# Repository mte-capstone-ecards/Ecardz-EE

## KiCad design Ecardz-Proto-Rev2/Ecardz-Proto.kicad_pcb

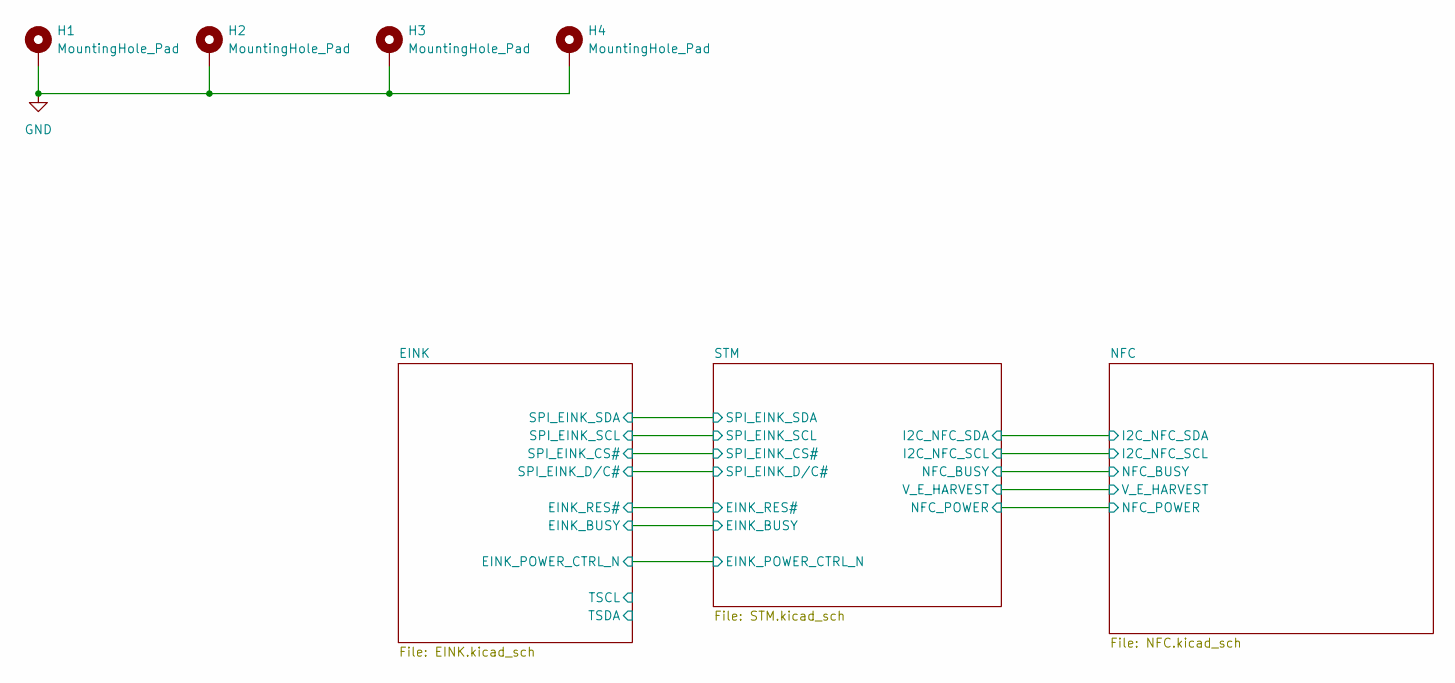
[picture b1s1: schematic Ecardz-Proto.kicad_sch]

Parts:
H1, H2, H3, H4: MountingHole_Pad; MountingHole_2.2mm_M2_DIN965

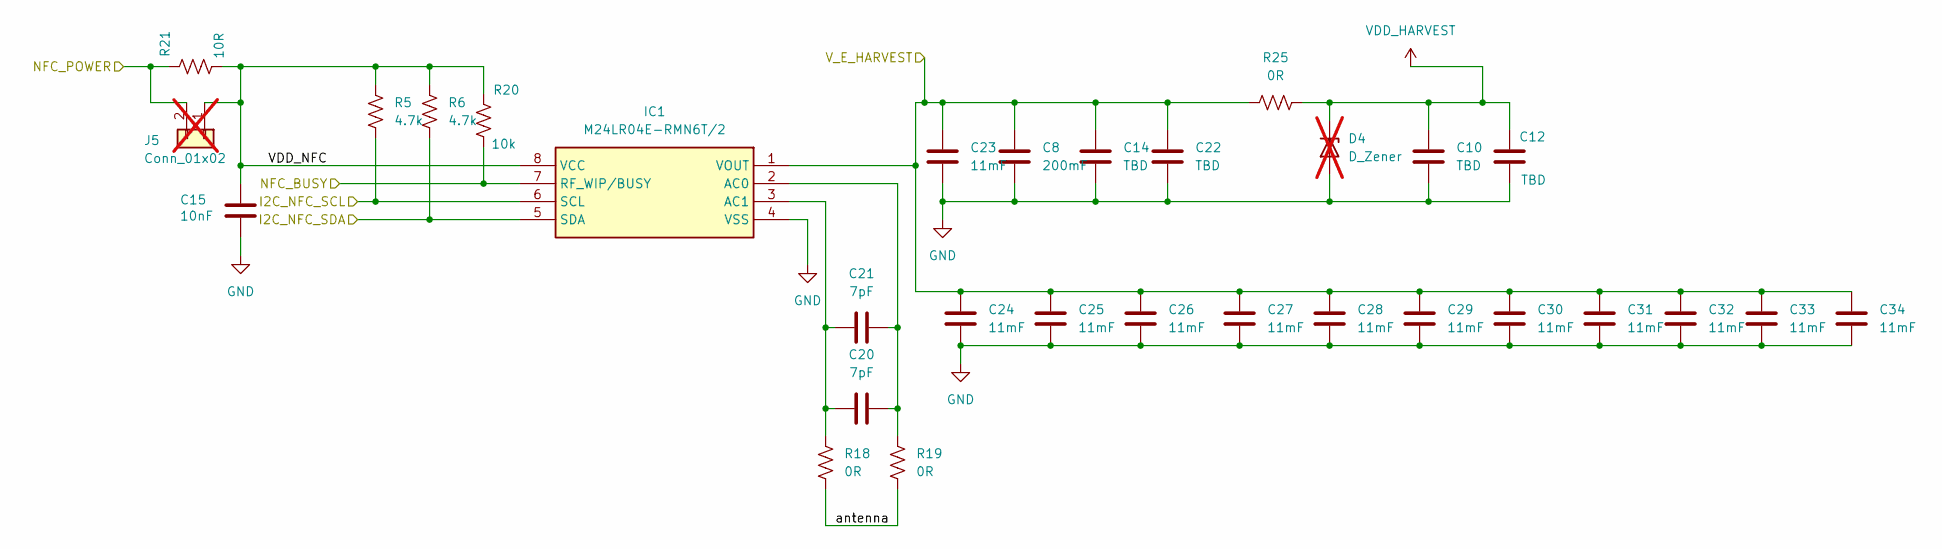
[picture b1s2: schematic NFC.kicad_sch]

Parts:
C8: 200mF; RSCSK2043R3D01004T; Digikey Part Number SCSK2043R3D01004T
C10, C12: TBD; C_0603_1608Metric_Pad1.08x0.95mm_HandSolder
C14, C22: TBD; C_2917
C15: 10nF; C_0603_1608Metric_Pad1.08x0.95mm_HandSolder; MANUFACTURER PART NUMBER C0603C102K5RACTU; Digikey Part Number 399-C0603C102K5RACTUTR-ND
C20, C21: 7pF; C_0603_1608Metric_Pad1.08x0.95mm_HandSolder; MANUFACTURER PART NUMBER GRM0335C1E7R0CA01D; Digikey Part Number 490-13324-2-ND
C23, C24, C25, C26, C27, C28, C29, C30, C31, C32, C33, C34: 11mF; CPH3225A; Digikey Part Number CPH3225A
D4: D_Zener; D_SOD-123; MANUFACTURER PART NUMBER MMSZ4684T1G; Digikey Part Number MMSZ4684T1GOSTR-ND; not fitted
IC1: M24LR04E-RMN6T/2; SO-8_3.9x4.9mm_P1.27mm; Mouser Part Number 511-M24LR04E-RDW6T/2
J5: Conn_01x02; PinHeader_1x02_P2.54mm_Vertical; not fitted
R5, R6: 4.7k; R_0603_1608Metric_Pad0.98x0.95mm_HandSolder; Part Number ERJ-3EKF4701V
R18, R19, R25: 0R; R_0603_1608Metric_Pad0.98x0.95mm_HandSolder; MANUFACTURER PART NUMBER CRCW0603590RFKEA; Digikey Part Number 541-590HTR-ND
R20: 10k; R_0603_1608Metric_Pad0.98x0.95mm_HandSolder; MANUFACTURER PART NUMBER RC0603FR-0710KL; Digikey Part Number 311-10.0KHRTR-ND
R21: 10R; R_0603_1608Metric_Pad0.98x0.95mm_HandSolder; MANUFACTURER PART NUMBER NRC06J100TRF

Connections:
/NFC/NFC_POWER: J5.2, R21.1; also elsewhere on the board
/NFC/VDD_NFC: C15.1, IC1.8 (VCC), J5.1, R5.1, R6.1, R20.1, R21.2
/NFC/V_E_HARVEST: C8.1, C14.1, C22.1, C23.1, C24.1, C25.1, C26.1, C27.1, C28.1, C29.1, C30.1, C31.1, C32.1, C33.1, C34.1, IC1.1 (VOUT), R25.1; also elsewhere on the board
/NFC/antenna: R18.1, R19.1
/STM/I2C_NFC_SCL: IC1.6 (SCL), R5.2; also elsewhere on the board
/STM/I2C_NFC_SDA: IC1.5 (SDA), R6.2; also elsewhere on the board
/STM/NFC_BUSY: IC1.7 (RF_WIP/BUSY), R20.2; also elsewhere on the board
GND: C8.2, C10.2, C12.2, C14.2, C15.2, C22.2, C23.2, C24.2, C25.2, C26.2, C27.2, C28.2, C29.2, C30.2, C31.2, C32.2, C33.2, C34.2, D4.2 (A), IC1.4 (VSS); also elsewhere on the board
unnamed: C20.2, C21.2, IC1.2 (AC0), R19.2
unnamed: C20.1, C21.1, IC1.3 (AC1), R18.2
VDD_HARVEST: C10.1, C12.1, D4.1 (K), R25.2; also elsewhere on the board

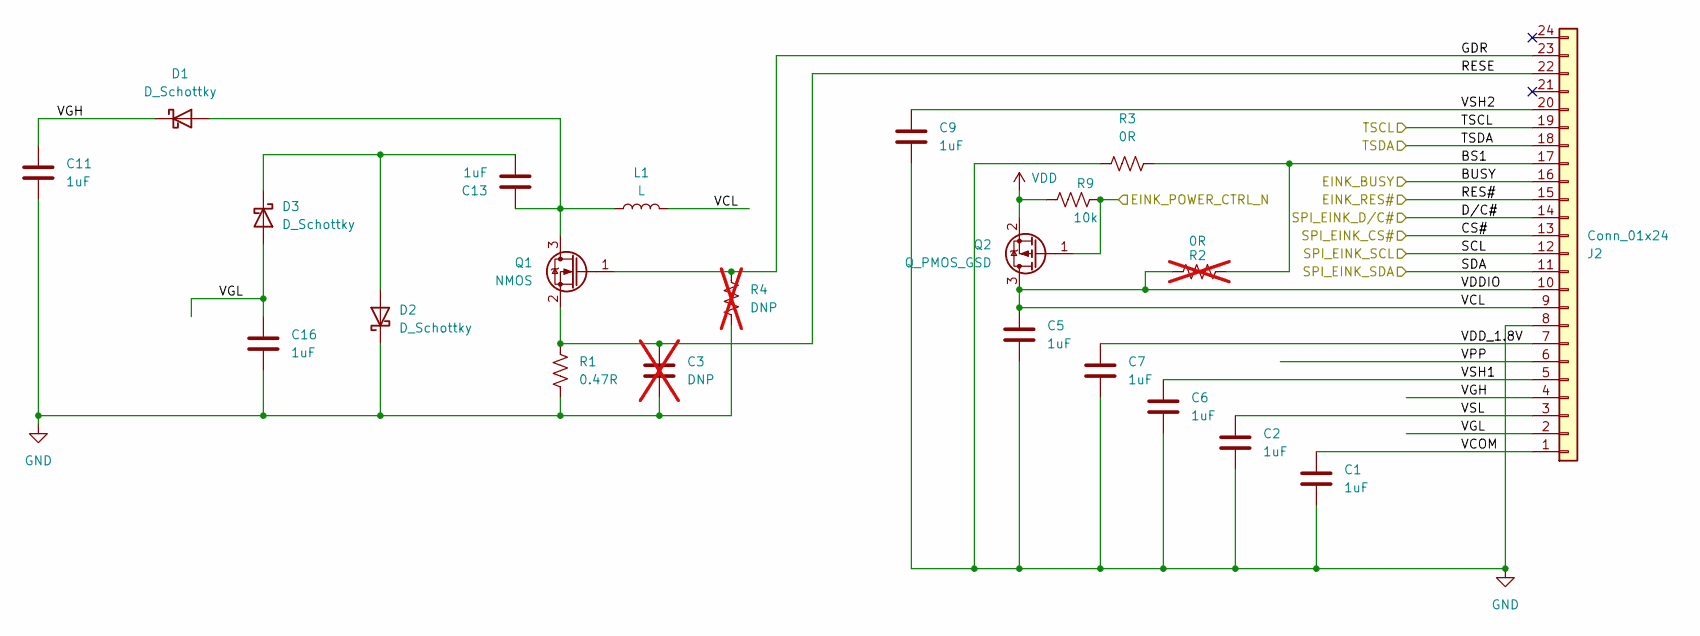
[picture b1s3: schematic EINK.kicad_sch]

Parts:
C1, C2, C5, C6, C7, C9, C11, C13, C16: 1uF; C_0603_1608Metric_Pad1.08x0.95mm_HandSolder; MANUFACTURER PART NUMBER CC0603KRX5R8BB105; Digikey Part Number 311-1445-2-ND
C3: DNP; C_0603_1608Metric_Pad1.08x0.95mm_HandSolder; MANUFACTURER PART NUMBER 100pF; not fitted
D1, D2, D3: D_Schottky; D_SOD-123; MANUFACTURER PART NUMBER MBR0530T1G; Digikey Part Number MBR0530T1GOSTR-ND
J2: Conn_01x24; TE_2-1734839-4_1x24-1MP_P0.5mm_Horizontal; MANUFACTURER PART NUMBER 4-1734839-5; Digikey Part Number A101358TR-ND
L1: L; CDRH5D18; MANUFACTURER PART NUMBER CDRH5D18NP-470NC; Digikey Part Number 308-2060-2-ND
Q1: NMOS; SOT-23; MANUFACTURER PART NUMBER IRLML2803TRPBF; Digikey Part Number IRLML2803PBFTR-ND
Q2: Q_PMOS_GSD; SOT-23; MANUFACTURER PART NUMBER BSS138NH6433XTMA1
R1: 0.47R; R_0603_1608Metric_Pad0.98x0.95mm_HandSolder; MANUFACTURER PART NUMBER ERJ-3RQJR47V; Digikey Part Number ERJ-3RQJR47V
R2: 0R; R_0603_1608Metric_Pad0.98x0.95mm_HandSolder; MANUFACTURER PART NUMBER RC0603JR-070RL; Digikey Part Number 311-0.0GRTR-ND; not fitted
R3: 0R; R_0603_1608Metric_Pad0.98x0.95mm_HandSolder; MANUFACTURER PART NUMBER RC0603JR-070RL; Digikey Part Number 311-0.0GRTR-ND
R4: DNP; R_0603_1608Metric_Pad0.98x0.95mm_HandSolder; MANUFACTURER PART NUMBER 100kR; not fitted
R9: 10k; R_0603_1608Metric_Pad0.98x0.95mm_HandSolder; MANUFACTURER PART NUMBER RC0603FR-0710KL; Digikey Part Number 311-10.0KHRTR-ND

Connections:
/EINK/BS1: J2.17, R2.2, R3.2
/EINK/BUSY: J2.16; also elsewhere on the board
/EINK/CS#: J2.13; also elsewhere on the board
/EINK/D/C#: J2.14; also elsewhere on the board
/EINK/EINK_POWER_CTRL_N: Q2.1 (G), R9.2; also elsewhere on the board
/EINK/GDR: J2.23, Q1.1 (G), R4.1
/EINK/RES#: J2.15; also elsewhere on the board
/EINK/RESE: C3.1, J2.22, Q1.2 (S), R1.1
/EINK/SCL: J2.12; also elsewhere on the board
/EINK/SDA: J2.11; also elsewhere on the board
/EINK/TSCL: J2.19
/EINK/TSDA: J2.18
/EINK/VCL: C5.1, J2.9, J2.10, L1.2, Q2.3 (D), R2.1
/EINK/VCOM: C1.1, J2.1
/EINK/VDD_1.8V: C7.1, J2.7
/EINK/VGH: C11.1, D1.1 (K), J2.4
/EINK/VGL: C16.1, D3.2 (A), J2.2
/EINK/VPP: J2.6
/EINK/VSH1: C6.1, J2.5
/EINK/VSH2: C9.1, J2.20
/EINK/VSL: C2.1, J2.3
GND: C1.2, C2.2, C3.2, C5.2, C6.2, C7.2, C9.2, C11.2, C16.2, D2.1 (K), J2.8, R1.2, R3.1, R4.2; also elsewhere on the board
unnamed: C13.1, D1.2 (A), L1.1, Q1.3 (D)
unnamed: C13.2, D2.2 (A), D3.1 (K)
VDD: Q2.2 (S), R9.1; also elsewhere on the board

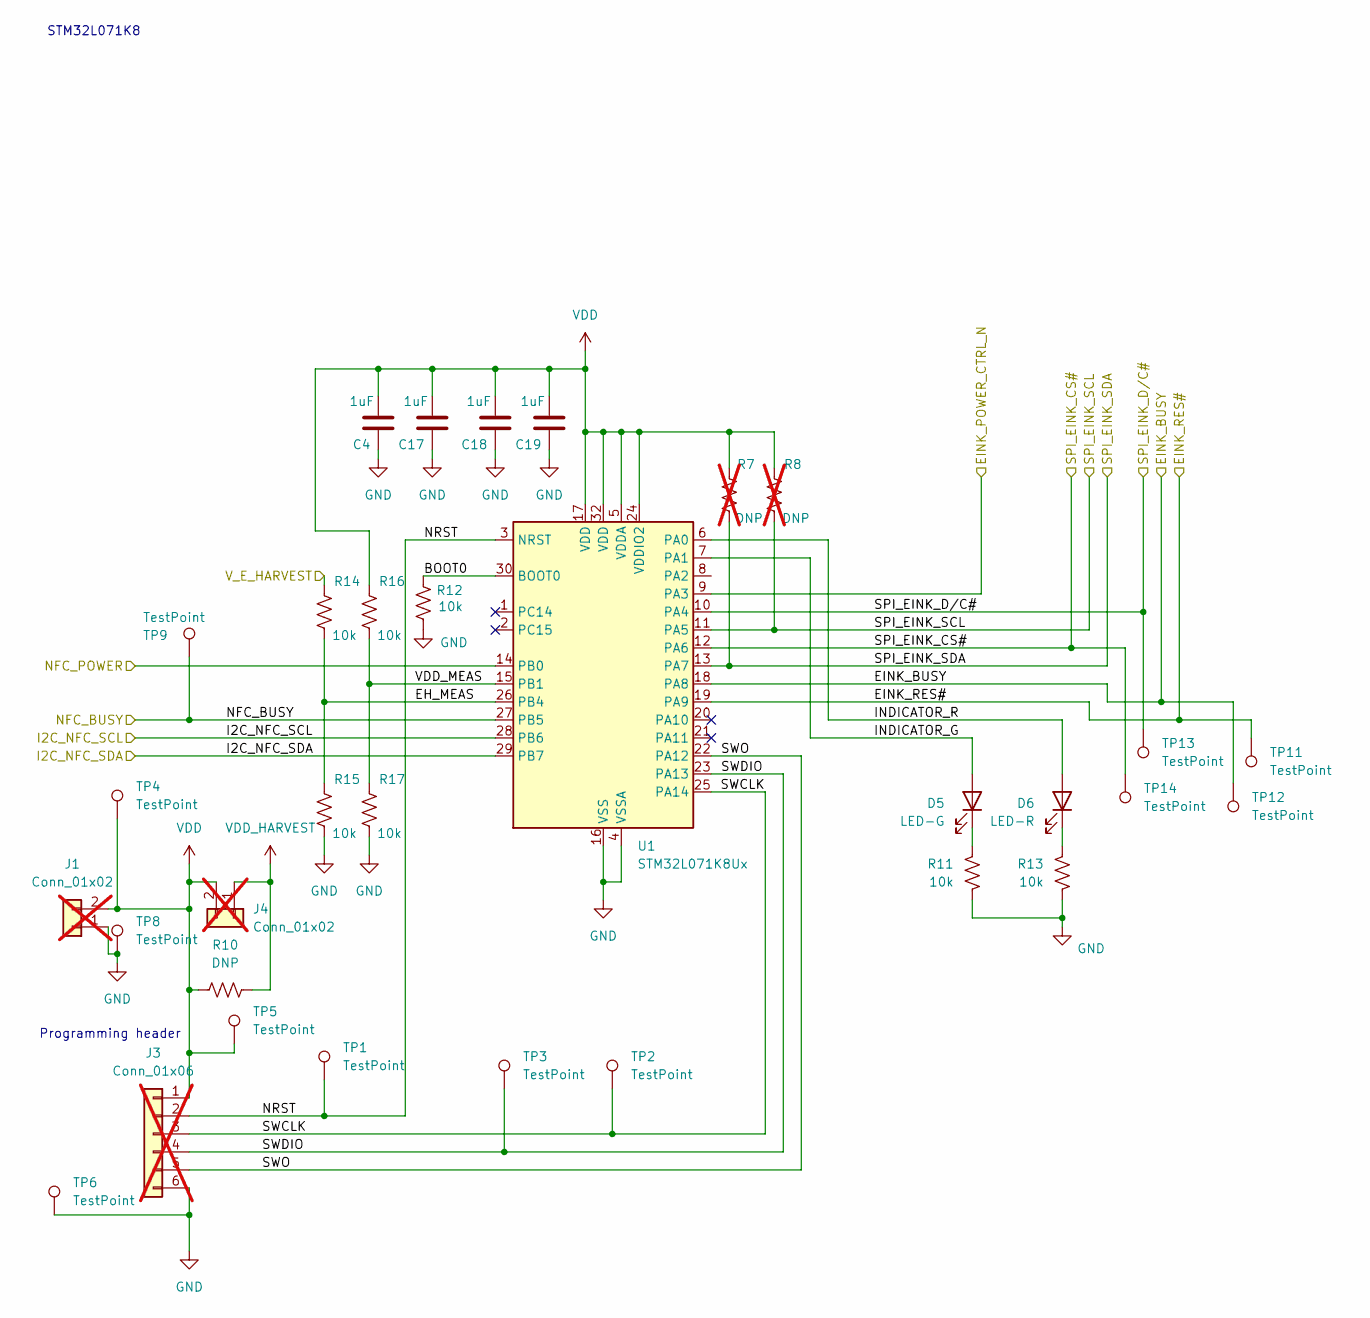
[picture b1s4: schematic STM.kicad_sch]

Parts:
C4, C17, C18, C19: 1uF; C_0603_1608Metric_Pad1.08x0.95mm_HandSolder; MANUFACTURER PART NUMBER CC0603KRX5R8BB105; Digikey Part Number 311-1445-2-ND
D5: LED-G; LED_0603_1608Metric_Pad1.05x0.95mm_HandSolder; MANUFACTURER PART NUMBER 150060GS75000
D6: LED-R; LED_0603_1608Metric_Pad1.05x0.95mm_HandSolder; MANUFACTURER PART NUMBER 150060RS75000
J1, J4: Conn_01x02; PinHeader_1x02_P2.54mm_Vertical; not fitted
J3: Conn_01x06; PinHeader_1x06_P2.54mm_Vertical; not fitted
R7, R8: DNP; R_0603_1608Metric_Pad0.98x0.95mm_HandSolder; MANUFACTURER PART NUMBER 100kR; not fitted
R10: DNP; R_0603_1608Metric_Pad0.98x0.95mm_HandSolder; MANUFACTURER PART NUMBER RC0603JR-070RL
R11, R13: 10k; R_0603_1608Metric_Pad0.98x0.95mm_HandSolder; Part Number RC0603FR-0710KL
R12, R14, R15, R16, R17: 10k; R_0603_1608Metric_Pad0.98x0.95mm_HandSolder; MANUFACTURER PART NUMBER RC0603FR-0710KL; Digikey Part Number 311-10.0KHRTR-ND
TP1, TP2, TP3, TP5, TP6, TP9, TP11, TP12, TP13, TP14: TestPoint; TestPoint_Pad_2.0x2.0mm
TP4, TP8: TestPoint; TestPoint_Pad_D1.5mm
U1: STM32L071K8Ux; QFN-32-1EP_5x5mm_P0.5mm_EP3.45x3.45mm; MANUFACTURER PART NUMBER STM32L071K8U6; Digikey Part Number 497-18576-ND

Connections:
/EINK/BUSY: TP12.1, U1.18 (PA8); also elsewhere on the board
/EINK/CS#: TP14.1, U1.12 (PA6); also elsewhere on the board
/EINK/D/C#: TP13.1, U1.10 (PA4); also elsewhere on the board
/EINK/EINK_POWER_CTRL_N: U1.9 (PA3); also elsewhere on the board
/EINK/RES#: TP11.1, U1.19 (PA9); also elsewhere on the board
/EINK/SCL: R8.2, U1.11 (PA5); also elsewhere on the board
/EINK/SDA: R7.2, U1.13 (PA7); also elsewhere on the board
/NFC/NFC_POWER: U1.14 (PB0); also elsewhere on the board
/NFC/V_E_HARVEST: R14.1; also elsewhere on the board
/STM/BOOT0: R12.1, U1.30 (BOOT0)
/STM/EH_MEAS: R14.2, R15.1, U1.26 (PB4)
/STM/I2C_NFC_SCL: U1.28 (PB6); also elsewhere on the board
/STM/I2C_NFC_SDA: U1.29 (PB7); also elsewhere on the board
/STM/INDICATOR_G: D5.2 (A), U1.7 (PA1)
/STM/INDICATOR_R: D6.2 (A), U1.6 (PA0)
/STM/NFC_BUSY: TP9.1, U1.27 (PB5); also elsewhere on the board
/STM/NRST: J3.2, TP1.1, U1.3 (NRST)
/STM/SWCLK: J3.3, TP2.1, U1.25 (PA14)
/STM/SWDIO: J3.4, TP3.1, U1.23 (PA13)
/STM/SWO: J3.5, U1.22 (PA12)
/STM/VDD_MEAS: R16.2, R17.1, U1.15 (PB1)
GND: C4.1, C17.1, C18.1, C19.1, J1.1, J3.6, R11.2, R12.2, R13.2, R15.2, R17.2, TP6.1, TP8.1, U1.4 (VSSA), U1.16 (VSS), U1.31 (VSS), U1.33 (VSS); also elsewhere on the board
unnamed: D5.1 (K), R11.1
unnamed: D6.1 (K), R13.1
VDD: C4.2, C17.2, C18.2, C19.2, J1.2, J3.1, J4.2, R7.1, R8.1, R10.1, R16.1, TP4.1, TP5.1, U1.5 (VDDA), U1.17 (VDD), U1.24 (VDDIO2), U1.32 (VDD); also elsewhere on the board
VDD_HARVEST: J4.1, R10.2; also elsewhere on the board

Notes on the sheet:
STM32L071K8
Programming header

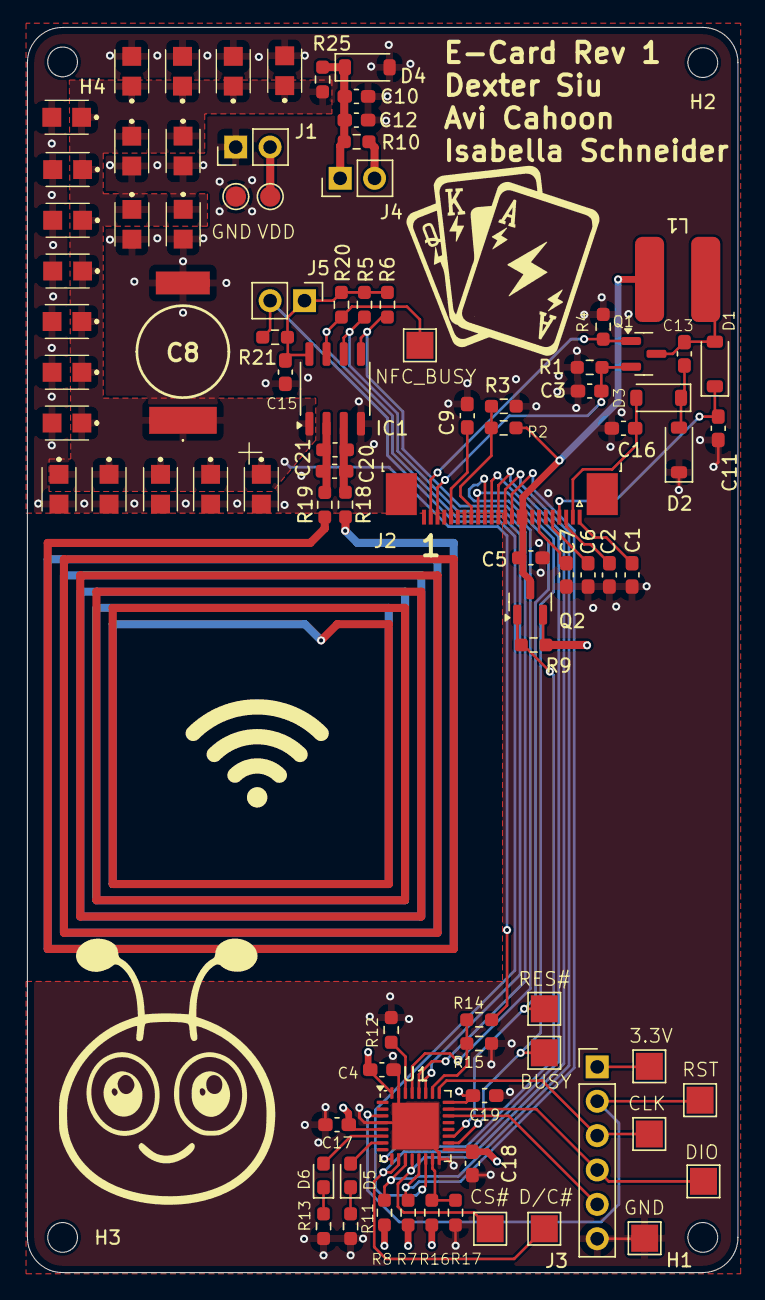
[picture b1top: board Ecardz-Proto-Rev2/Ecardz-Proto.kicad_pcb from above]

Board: 4 copper layers, 52.5 x 92.0 mm, 94 parts (0 on the bottom side), 43 nets.

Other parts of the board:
C23#2, C23#3, C26#2, C26#3, C26#4, C30#2, C30#3, C30#4: 11mF; CPH3225A

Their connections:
/NFC/V_E_HARVEST: C23#2.1, C23#3.1, C26#2.1, C26#3.1, C26#4.1, C30#2.1, C30#3.1, C30#4.1; also elsewhere on the board
GND: C23#2.2, C23#3.2, C26#2.2, C26#3.2, C26#4.2, C30#2.2, C30#3.2, C30#4.2; also elsewhere on the board

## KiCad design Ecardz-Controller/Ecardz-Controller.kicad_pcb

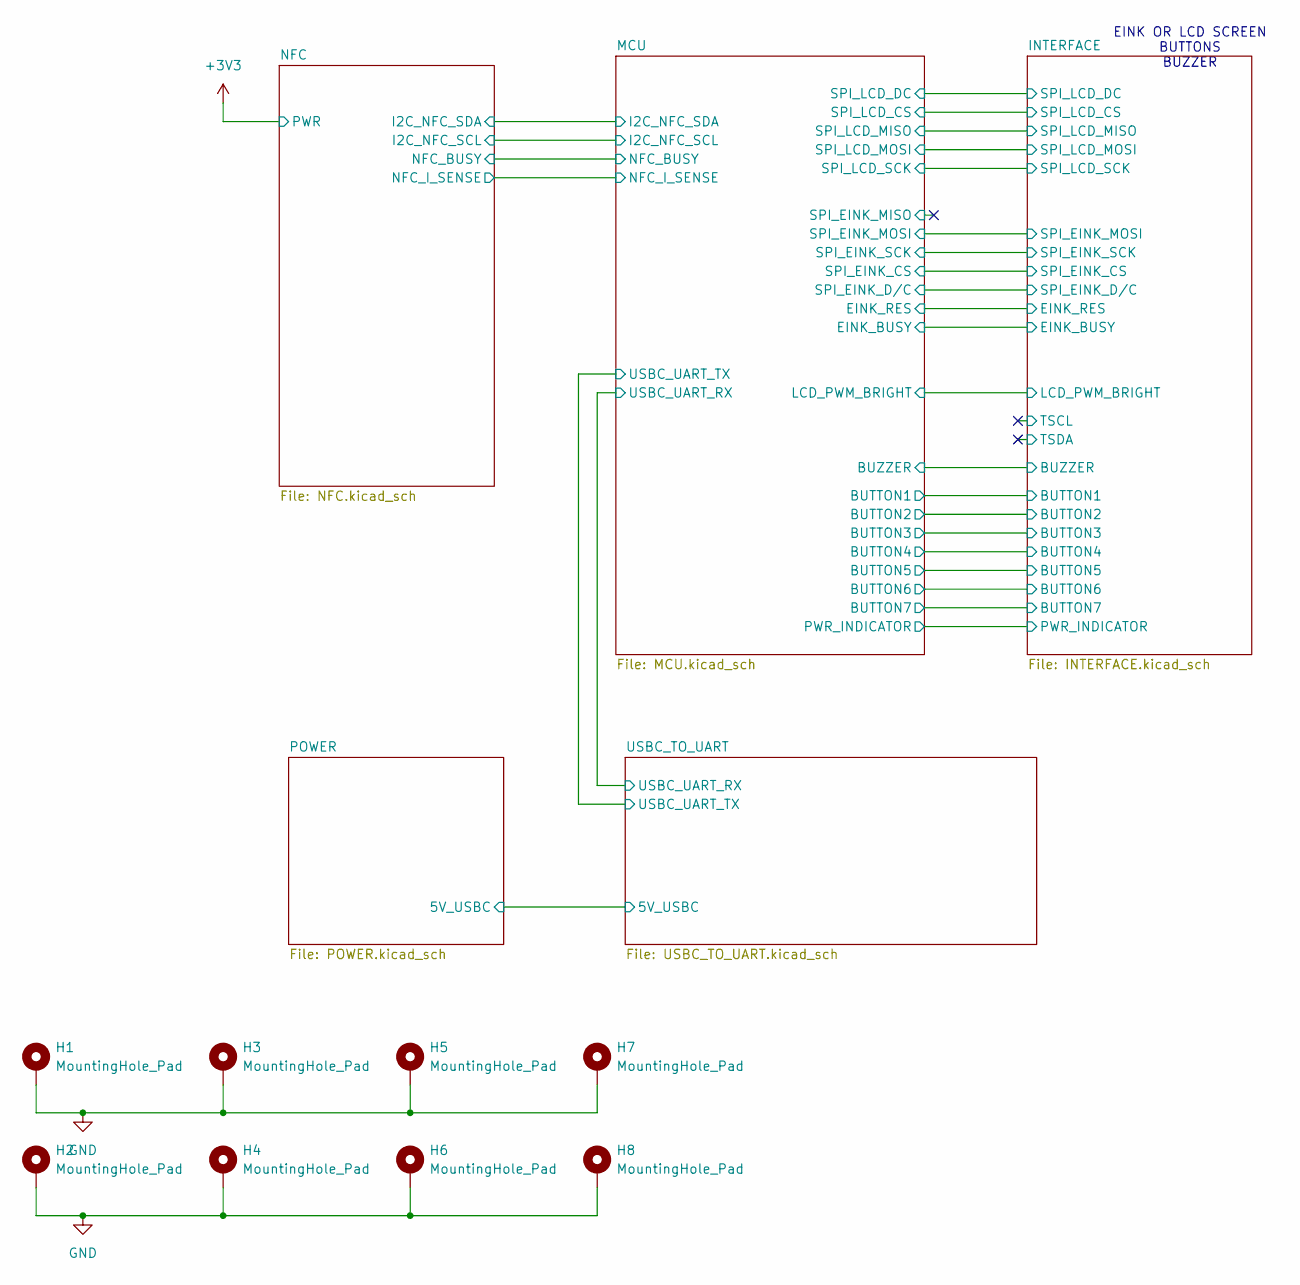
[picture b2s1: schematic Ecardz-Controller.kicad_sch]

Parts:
H1, H2, H3, H4, H5, H6, H7, H8: MountingHole_Pad; MountingHole_2.7mm_M2.5_Pad_TopBottom

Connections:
GND: H1.1, H2.1, H3.1, H4.1, H5.1, H6.1, H7.1, H8.1; also elsewhere on the board

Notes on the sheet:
EINK OR LCD SCREEN BUTTONS BUZZER

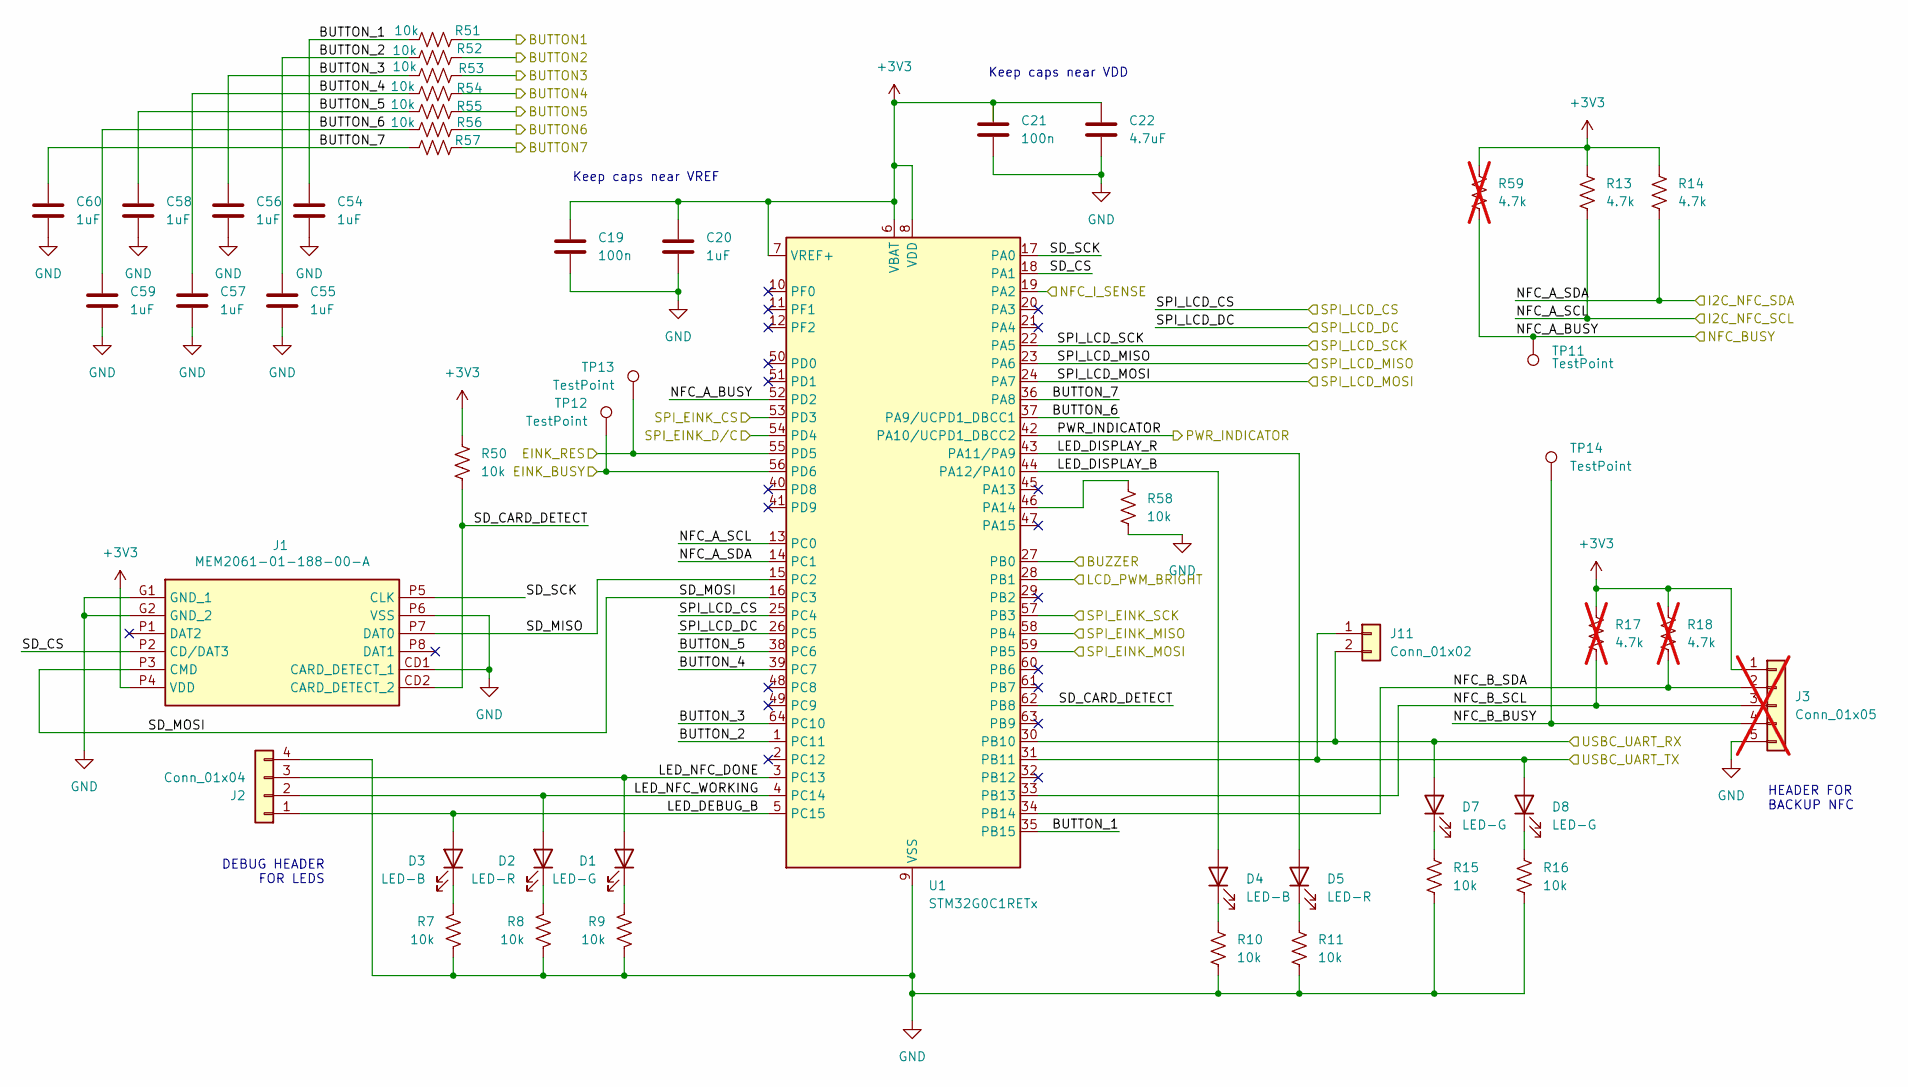
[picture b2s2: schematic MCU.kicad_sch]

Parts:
C19, C21: 100n; C_0603_1608Metric_Pad1.08x0.95mm_HandSolder; Part Number CC0603KRX7R7BB104
C20, C54, C55, C56, C57, C58, C59, C60: 1uF; C_0603_1608Metric_Pad1.08x0.95mm_HandSolder; Part Number CC0603KRX5R8BB105
C22: 4.7uF; C_0603_1608Metric_Pad1.08x0.95mm_HandSolder; Part Number CL10A475KP8NNNC
D1, D7, D8: LED-G; LED_0603_1608Metric_Pad1.05x0.95mm_HandSolder; Part Number 150060GS75000
D2, D5: LED-R; LED_0603_1608Metric_Pad1.05x0.95mm_HandSolder; Part Number 150060RS75000
D3, D4: LED-B; LED_0603_1608Metric_Pad1.05x0.95mm_HandSolder; Part Number 150060BS75000
J1: MEM2061-01-188-00-A; MEM20610118800A; Mouser Part Number 640-MEM20610118800A
J2: Conn_01x04; PinHeader_1x04_P2.54mm_Horizontal; Part Number 61300411121
J3: Conn_01x05; PinHeader_1x05_P2.54mm_Horizontal; Part Number 61300511121; not fitted
J11: Conn_01x02; PinHeader_1x02_P2.54mm_Horizontal
R7, R8, R9, R10, R11, R15, R16, R50, R51, R52, R53, R54, R55, R56, R57, R58: 10k; R_0603_1608Metric_Pad0.98x0.95mm_HandSolder; Part Number RC0603FR-0710KL
R13, R14: 4.7k; R_0603_1608Metric_Pad0.98x0.95mm_HandSolder; Part Number ERJ-3EKF4701V
R17, R18, R59: 4.7k; R_0603_1608Metric_Pad0.98x0.95mm_HandSolder; Part Number ERJ-3EKF4701V; not fitted
TP11, TP12, TP13, TP14: TestPoint; TestPoint_Pad_D3.0mm
U1: STM32G0C1RETx; LQFP-64_10x10mm_P0.5mm; Part Number STM32G0C1RETx

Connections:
+3V3: C19.1, C20.1, C21.1, C22.1, J1.P4 (VDD), J3.1, R13.1, R14.1, R17.1, R18.1, R50.1, R59.1, U1.6 (VBAT), U1.7 (VREF+), U1.8 (VDD); also elsewhere on the board
/INTERFACE/BUSY: TP12.1, U1.56 (PD6); also elsewhere on the board
/INTERFACE/BUTTON1: R51.2; also elsewhere on the board
/INTERFACE/BUTTON2: R52.2; also elsewhere on the board
/INTERFACE/BUTTON3: R53.2; also elsewhere on the board
/INTERFACE/BUTTON4: R54.2; also elsewhere on the board
/INTERFACE/BUTTON5: R55.2; also elsewhere on the board
/INTERFACE/BUTTON6: R56.2; also elsewhere on the board
/INTERFACE/BUTTON7: R57.2; also elsewhere on the board
/INTERFACE/BUZZER: U1.27 (PB0); also elsewhere on the board
/INTERFACE/CS#: U1.53 (PD3); also elsewhere on the board
/INTERFACE/D/C#: U1.54 (PD4); also elsewhere on the board
/INTERFACE/LCD_PWM_BRIGHT: U1.28 (PB1); also elsewhere on the board
/INTERFACE/RES#: TP13.1, U1.55 (PD5); also elsewhere on the board
/INTERFACE/SCL: U1.57 (PB3); also elsewhere on the board
/INTERFACE/SDA: U1.59 (PB5); also elsewhere on the board
/MCU/BUTTON_1: C54.1, R51.1, U1.35 (PB15)
/MCU/BUTTON_2: C55.1, R52.1, U1.1 (PC11)
/MCU/BUTTON_3: C56.1, R53.1, U1.64 (PC10)
/MCU/BUTTON_4: C57.1, R54.1, U1.39 (PC7)
/MCU/BUTTON_5: C58.1, R55.1, U1.38 (PC6)
/MCU/BUTTON_6: C59.1, R56.1, U1.37 (PA9/UCPD1_DBCC1)
/MCU/BUTTON_7: C60.1, R57.1, U1.36 (PA8)
/MCU/LED_DEBUG_B: D3.2 (A), J2.1, U1.5 (PC15)
/MCU/LED_DISPLAY_B: D4.2 (A), U1.44 (PA12/PA10)
/MCU/LED_DISPLAY_R: D5.2 (A), U1.43 (PA11/PA9)
/MCU/LED_NFC_DONE: D1.2 (A), J2.3, U1.3 (PC13)
/MCU/LED_NFC_WORKING: D2.2 (A), J2.2, U1.4 (PC14)
/MCU/NFC_A_BUSY: R59.2, TP11.1, U1.52 (PD2); also elsewhere on the board
/MCU/NFC_A_SCL: R13.2, U1.13 (PC0); also elsewhere on the board
/MCU/NFC_A_SDA: R14.2, U1.14 (PC1); also elsewhere on the board
/MCU/NFC_B_BUSY: J3.4, TP14.1
/MCU/NFC_B_SCL: J3.3, R17.2, U1.33 (PB13)
/MCU/NFC_B_SDA: J3.2, R18.2, U1.34 (PB14)
/MCU/NFC_I_SENSE: U1.19 (PA2); also elsewhere on the board
/MCU/PWR_INDICATOR: U1.42 (PA10/UCPD1_DBCC2); also elsewhere on the board
/MCU/SD_CARD_DETECT: J1.CD2 (CARD_DETECT_2), R50.2, U1.62 (PB8)
/MCU/SD_CS: J1.P2 (CD/DAT3), U1.18 (PA1)
/MCU/SD_MISO: J1.P7 (DAT0), U1.15 (PC2)
/MCU/SD_MOSI: J1.P3 (CMD), U1.16 (PC3)
/MCU/SD_SCK: J1.P5 (CLK), U1.17 (PA0)
/MCU/SPI_EINK_MISO: U1.58 (PB4)
/MCU/SPI_LCD_CS: U1.25 (PC4); also elsewhere on the board
/MCU/SPI_LCD_DC: U1.26 (PC5); also elsewhere on the board
/MCU/SPI_LCD_MISO: U1.23 (PA6); also elsewhere on the board
/MCU/SPI_LCD_MOSI: U1.24 (PA7); also elsewhere on the board
/MCU/SPI_LCD_SCK: U1.22 (PA5); also elsewhere on the board
/MCU/USBC_UART_RX: D7.2 (A), J11.2, U1.30 (PB10); also elsewhere on the board
/MCU/USBC_UART_TX: D8.2 (A), J11.1, U1.31 (PB11); also elsewhere on the board
GND: C19.2, C20.2, C21.2, C22.2, C54.2, C55.2, C56.2, C57.2, C58.2, C59.2, C60.2, J1.CD1 (CARD_DETECT_1), J1.G1 (GND_1), J1.G2 (GND_2), J1.P6 (VSS), J2.4, J3.5, R7.2, R8.2, R9.2, R10.2, R11.2, R15.2, R16.2, R58.2, U1.9 (VSS); also elsewhere on the board
unnamed: D1.1 (K), R9.1
unnamed: D2.1 (K), R8.1
unnamed: D3.1 (K), R7.1
unnamed: D4.1 (K), R10.1
unnamed: D5.1 (K), R11.1
unnamed: D7.1 (K), R15.1
unnamed: D8.1 (K), R16.1
unnamed: R58.1, U1.46 (PA14)

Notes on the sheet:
HEADER FOR BACKUP NFC
DEBUG HEADER FOR LEDS
Keep caps near VDD
Keep caps near VREF

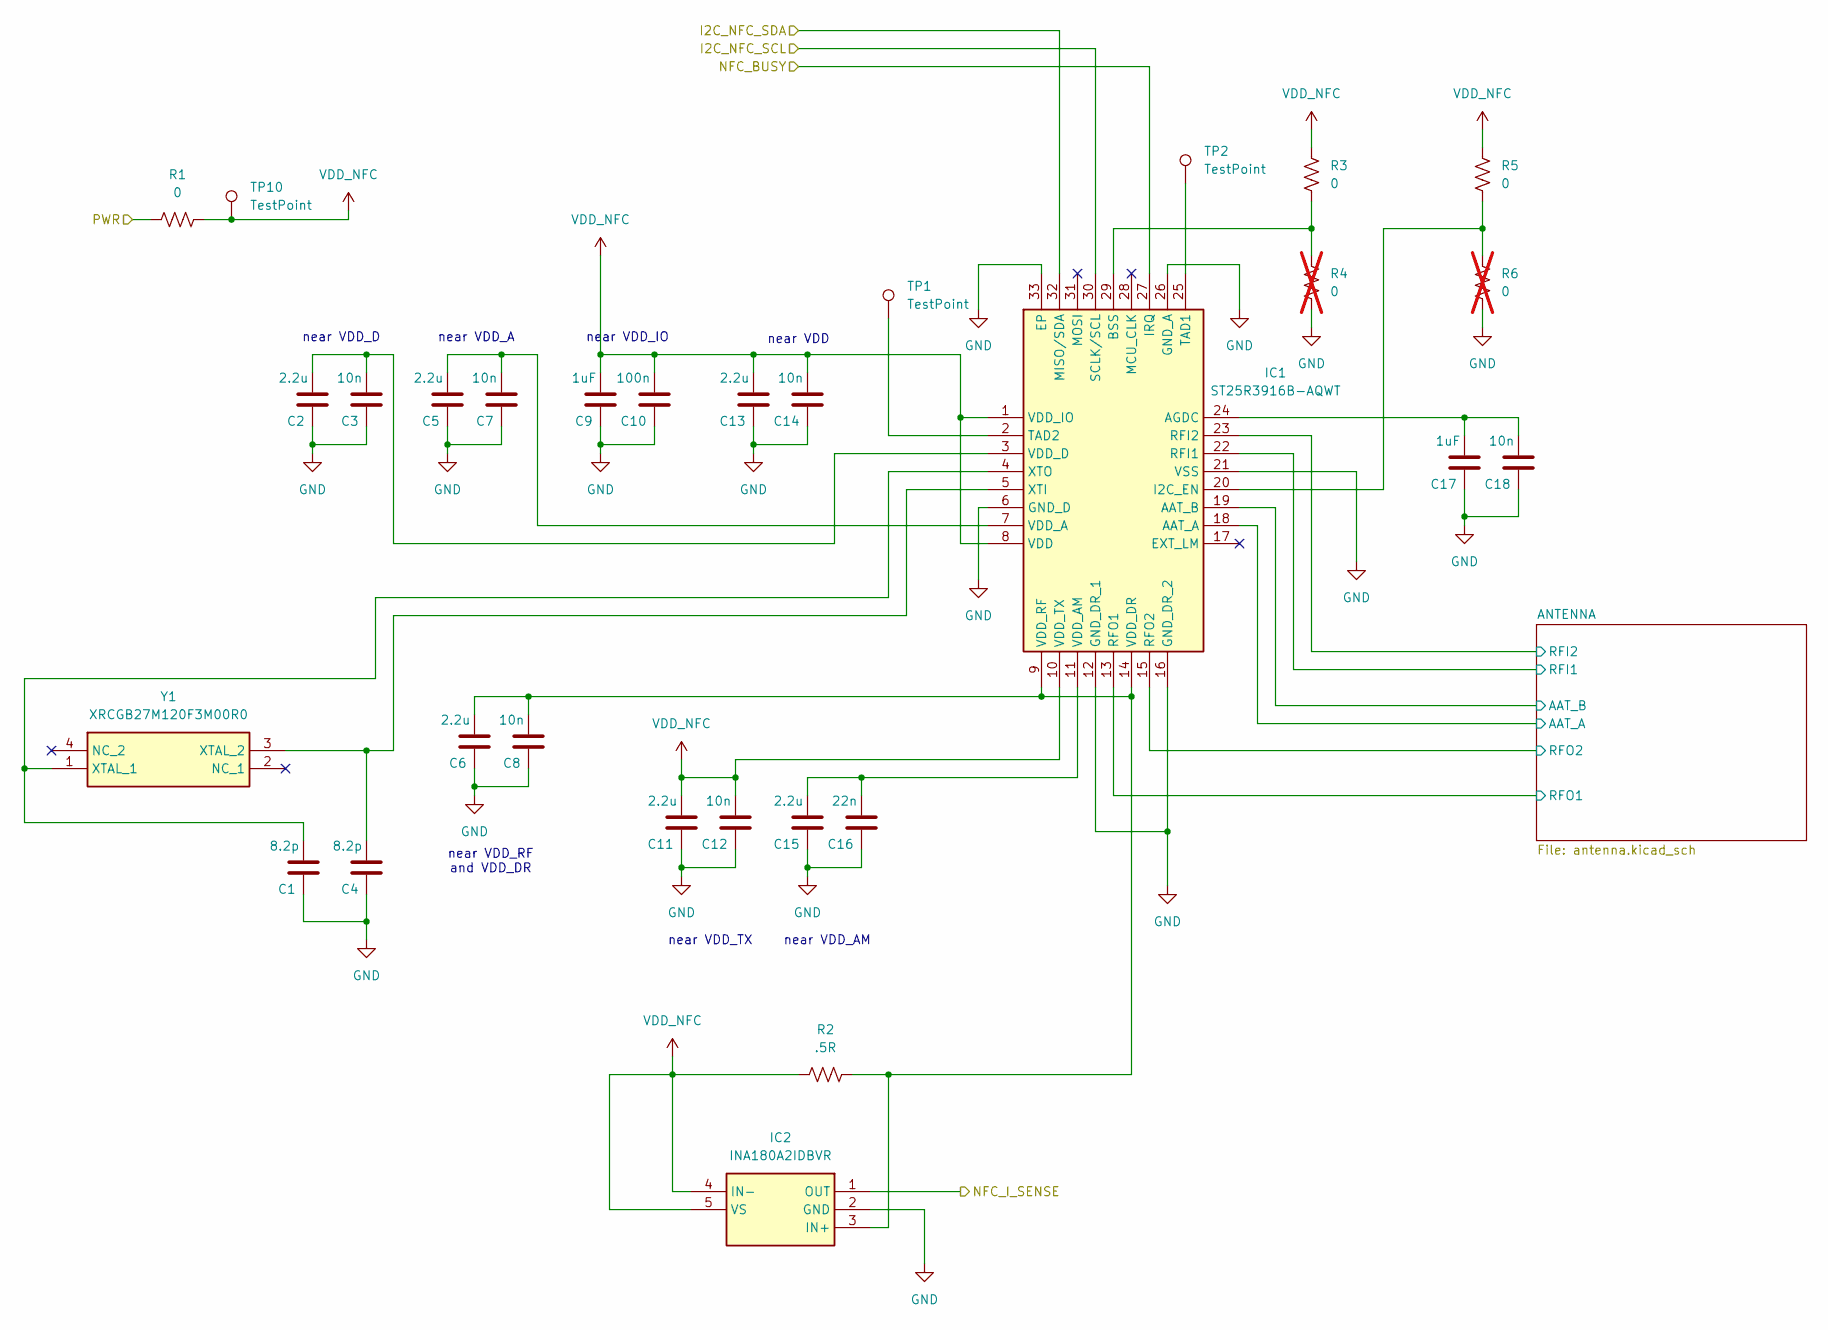
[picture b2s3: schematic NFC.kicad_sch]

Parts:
C1, C4: 8.2p; C_0603_1608Metric_Pad1.08x0.95mm_HandSolder; MANUFACTURER PART NUMBER CC0603KRX5R8BB105; Digikey Part Number 311-1445-2-ND
C2, C5, C6, C11, C13, C15: 2.2u; C_0603_1608Metric_Pad1.08x0.95mm_HandSolder; MANUFACTURER PART NUMBER CC0603KRX5R8BB105; Digikey Part Number 311-1445-2-ND
C3, C7, C8, C12, C14, C18: 10n; C_0603_1608Metric_Pad1.08x0.95mm_HandSolder; MANUFACTURER PART NUMBER CC0603KRX5R8BB105; Digikey Part Number 311-1445-2-ND
C9, C17: 1uF; C_0603_1608Metric_Pad1.08x0.95mm_HandSolder; MANUFACTURER PART NUMBER CC0603KRX5R8BB105; Digikey Part Number 311-1445-2-ND
C10: 100n; C_0603_1608Metric_Pad1.08x0.95mm_HandSolder; MANUFACTURER PART NUMBER CC0603KRX5R8BB105; Digikey Part Number 311-1445-2-ND
C16: 22n; C_0603_1608Metric_Pad1.08x0.95mm_HandSolder; MANUFACTURER PART NUMBER CC0603KRX5R8BB105; Digikey Part Number 311-1445-2-ND
IC1: ST25R3916B-AQWT; QFN50P500X500X100-33N-D; Mouser Part Number 511-ST25R3916B-AQWT
IC2: INA180A2IDBVR; SOT95P280X145-5N; Mouser Part Number 595-INA180A2IDBVR
R1, R3, R5: 0; R_0603_1608Metric_Pad0.98x0.95mm_HandSolder; MANUFACTURER PART NUMBER CRCW0603590RFKEA; Digikey Part Number 541-590HTR-ND
R2: .5R; R_0603_1608Metric_Pad0.98x0.95mm_HandSolder; MANUFACTURER PART NUMBER CRCW0603590RFKEA; Digikey Part Number 541-590HTR-ND
R4, R6: 0; R_0603_1608Metric_Pad0.98x0.95mm_HandSolder; MANUFACTURER PART NUMBER CRCW0603590RFKEA; Digikey Part Number 541-590HTR-ND; not fitted
TP1, TP2, TP10: TestPoint; TestPoint_Pad_D3.0mm
Y1: XRCGB27M120F3M00R0; XRCGB; Mouser Part Number 81-XRCGB27M120F3M0R0

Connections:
+3V3: R1.2; also elsewhere on the board
/MCU/NFC_A_BUSY: IC1.27 (IRQ); also elsewhere on the board
/MCU/NFC_A_SCL: IC1.30 (SCLK/SCL); also elsewhere on the board
/MCU/NFC_A_SDA: IC1.32 (MISO/SDA); also elsewhere on the board
/MCU/NFC_I_SENSE: IC2.1 (OUT); also elsewhere on the board
/NFC/ANTENNA/AAT_A: IC1.18 (AAT_A); also elsewhere on the board
/NFC/ANTENNA/AAT_B: IC1.19 (AAT_B); also elsewhere on the board
/NFC/ANTENNA/RFI1: IC1.22 (RFI1); also elsewhere on the board
/NFC/ANTENNA/RFI2: IC1.23 (RFI2); also elsewhere on the board
/NFC/ANTENNA/RFO1: IC1.13 (RFO1); also elsewhere on the board
/NFC/ANTENNA/RFO2: IC1.15 (RFO2); also elsewhere on the board
GND: C1.1, C2.1, C3.1, C4.1, C5.1, C6.1, C7.1, C8.1, C9.1, C10.1, C11.1, C12.1, C13.1, C14.1, C15.1, C16.1, C17.1, C18.1, IC1.6 (GND_D), IC1.12 (GND_DR_1), IC1.16 (GND_DR_2), IC1.21 (VSS), IC1.26 (GND_A), IC1.33 (EP), IC2.2 (GND), R4.1, R6.1; also elsewhere on the board
unnamed: C17.2, C18.2, IC1.24 (AGDC)
unnamed: IC1.29 (BSS), R3.1, R4.2
unnamed: IC1.20 (I2C_EN), R5.1, R6.2
unnamed: IC1.25 (TAD1), TP2.1
unnamed: IC1.2 (TAD2), TP1.1
unnamed: C5.2, C7.2, IC1.7 (VDD_A)
unnamed: C15.2, C16.2, IC1.11 (VDD_AM)
unnamed: C2.2, C3.2, IC1.3 (VDD_D)
unnamed: C6.2, C8.2, IC1.9 (VDD_RF), IC1.14 (VDD_DR), IC2.3 (IN+), R2.2
unnamed: C4.2, IC1.5 (XTI), Y1.3 (XTAL_2)
unnamed: C1.2, IC1.4 (XTO), Y1.1 (XTAL_1)
VDD_NFC: C9.2, C10.2, C11.2, C12.2, C13.2, C14.2, IC1.1 (VDD_IO), IC1.8 (VDD), IC1.10 (VDD_TX), IC2.4 (IN-), IC2.5 (VS), R1.1, R2.1, R3.2, R5.2, TP10.1

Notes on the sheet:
near VDD_RF and VDD_DR
near VDD_AM
near VDD
near VDD_IO
near VDD_A
near VDD_D
near VDD_TX
